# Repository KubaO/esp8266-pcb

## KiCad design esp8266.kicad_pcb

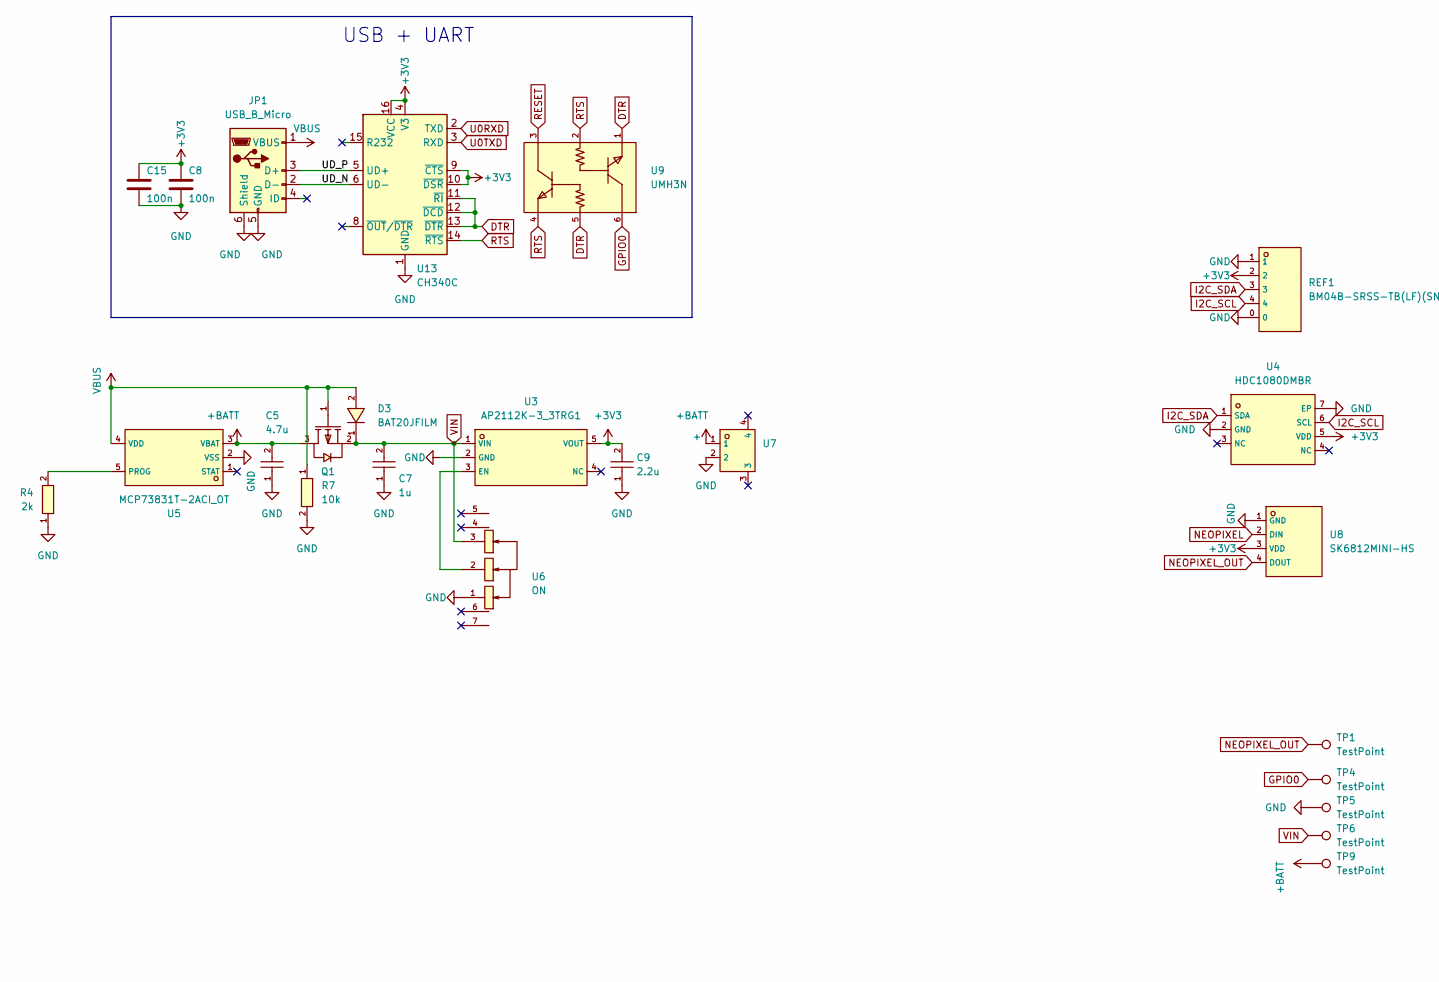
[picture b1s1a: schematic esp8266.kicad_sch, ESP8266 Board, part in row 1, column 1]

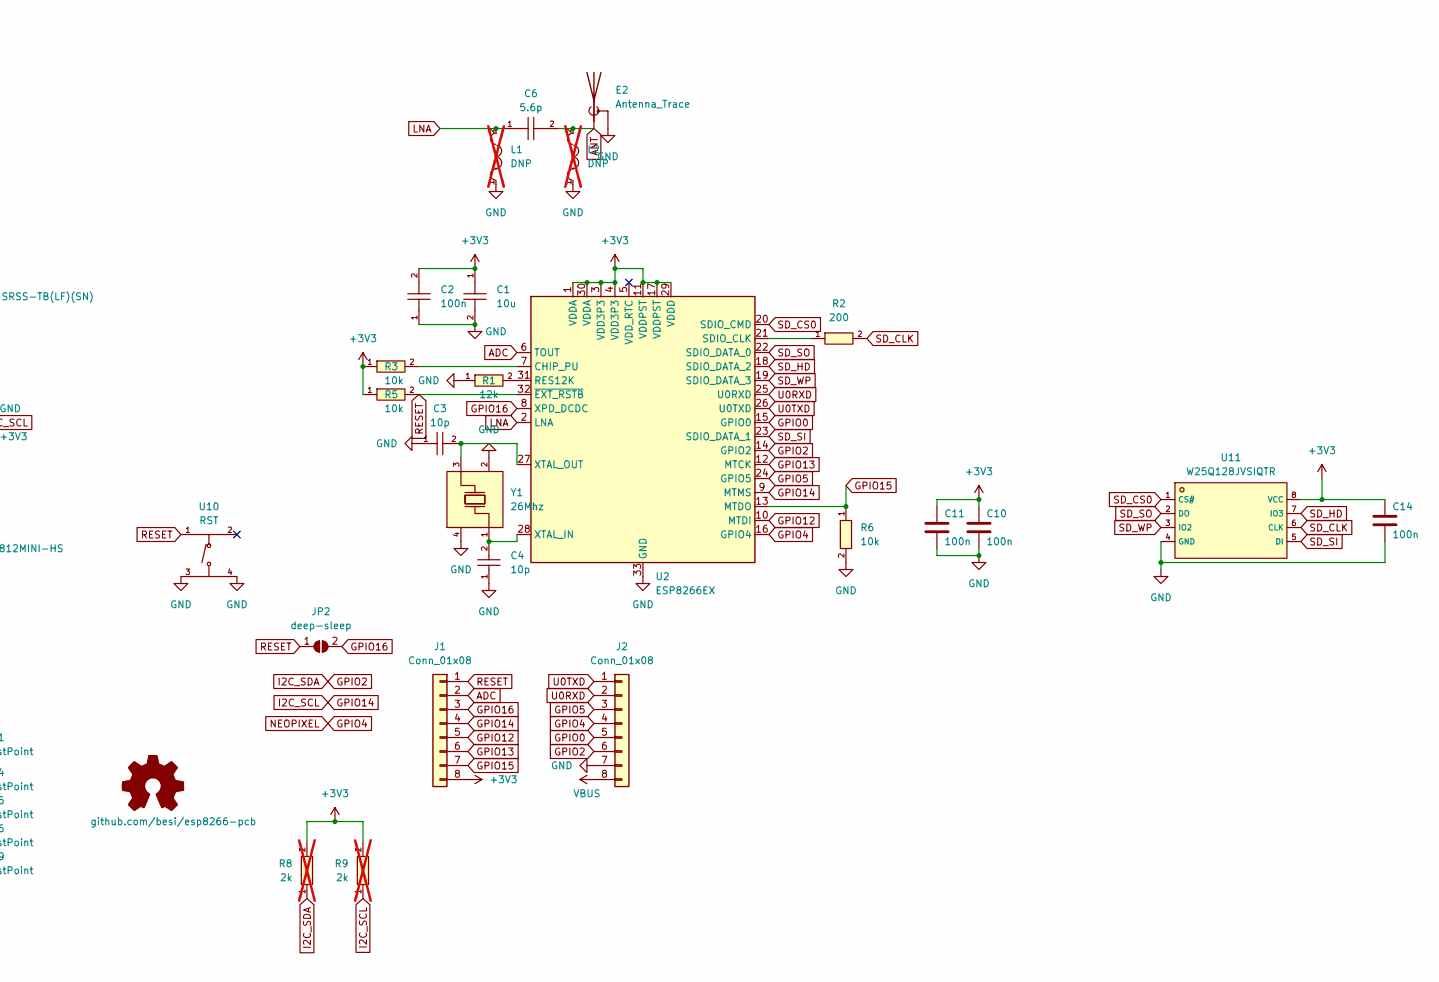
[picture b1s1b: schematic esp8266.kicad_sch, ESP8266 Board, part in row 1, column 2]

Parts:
C1: 10u; C0603; LCSC C19702
C2, C8, C10, C11, C14, C15: 100n; C0603; LCSC C14663
C3, C4: 10p; C0603; LCSC C1634
C5: 4.7u; C0603; LCSC C19666
C6: 5.6p; C0603; LCSC C519111
C7: 1u; C0603; LCSC C15849
C9: 2.2u; C0603; LCSC C23630
D3: BAT20JFILM; SOD-323_L1.8-W1.3-LS2.5-RD; LCSC C155590
E2: Antenna_Trace; Texas_SWRA117D_2.4GHz_Right
J1, J2: Conn_01x08; PinHeader_1x08_P2.54mm_Vertical
JP1: USB_B_Micro; MICRO-USB-SMD_1050171001; LCSC C505111
JP2: deep-sleep; SolderJumper-2_P1.3mm_Open_TrianglePad1.0x1.5mm
L1, L2: DNP; L0603; LCSC C1035; not fitted
OSHW1: github.com/besi/esp8266-pcb; OSHW-Symbol_6.7x6mm_SilkScreen
Q1: AO3401A; SOT-23_L2.9-W1.3-P1.90-LS2.4-BR; LCSC C15127
R1: 12k; R0603; LCSC C22790
R2: 200; R0603; LCSC C8218
R3, R5, R6, R7: 10k; R0603; LCSC C25804
R4: 2k; R0603; LCSC C22975
R8, R9: 2k; R0603; LCSC C22975; not fitted
REF1: BM04B-SRSS-TB(LF)(SN); CONN-SMD_BM04B-SRSS-TB; LCSC C160390
TP1, TP4, TP5, TP6, TP9: TestPoint; TestPoint_Pad_D1.0mm
U2: ESP8266EX; QFN-32_L5.0-W5.0-P0.50-BL-EP3.7
U3: AP2112K-3_3TRG1; SOT-25-5_L2.9-W1.6-P0.95-LS2.8-BL; LCSC C51118
U4: HDC1080DMBR; SENSOR-SMD_HDC1080DMBR; LCSC C82227
U5: MCP73831T-2ACI_OT; SOT-23-5_L3.0-W1.7-P0.95-LS2.8-BL; LCSC C424093
U6: ON; SW-SMD_MK-12C02-G020; LCSC C963206
U7: +; CONN-SMD_P2.00_S2B-PH-SM4-TB-LF-SN; LCSC C295747
U8: SK6812MINI-HS; LED-SMD_4P-L3.5-W3.5-BR_SK6812MINI-HS; LCSC C2922787
U9: UMH3N; SC-70-6_L2.2-W1.3-P0.65-LS2.1-BR; LCSC C62892
U10: RST; SW-SMD_4P-L5.1-W5.1-P3.70-LS6.5-TL-2; LCSC C318884
U11: W25Q128JVSIQTR; SOIC-8_L5.3-W5.3-P1.27-LS8.0-BL; LCSC C97521
U13: CH340C; SOIC-16_3.9x9.9mm_P1.27mm; LCSC C7464026
Y1: 26Mhz; CRYSTAL-SMD_4P-L2.0-W1.6-BL; LCSC C255886

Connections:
+3V3: C1.1, C2.2, C8.2, C9.2, C10.2, C11.2, C14.2, C15.2, J1.8, R3.1, R5.1, R8.2, R9.2, REF1.2, U2.1 (VDDA), U2.3 (VDD3P3), U2.4 (VDD3P3), U2.11 (VDDPST), U2.17 (VDDPST), U2.29 (VDDD), U2.30 (VDDA), U3.5 (VOUT), U4.5 (VDD), U8.3 (VDD), U11.8 (VCC), U13.4 (V3), U13.9 (~CTS), U13.10 (~DSR), U13.16 (VCC)
+BATT: C5.2, Q1.3 (D), TP9.1, U5.3 (VBAT), U7.1
/UD_N: JP1.2 (D-), U13.6 (UD-)
/UD_P: JP1.3 (D+), U13.5 (UD+)
ADC: J1.2, U2.6 (TOUT)
ANT: C6.2, E2.1 (A), L2.2
DTR: U9.1 (E), U9.5 (B), U13.11 (~RI), U13.12 (~DCD), U13.13 (~DTR)
GND: C1.2, C2.1, C3.1, C4.1, C5.1, C7.1, C8.1, C9.1, C10.1, C11.1, C14.1, C15.1, E2.2 (Shield), J2.7, JP1.5 (GND), JP1.6 (Shield), L1.1, L2.1, R1.1, R4.1, R6.2, R7.2, REF1.0, REF1.1, TP5.1, U2.33 (GND), U3.2 (GND), U4.2 (GND), U4.7 (EP), U5.2 (VSS), U6.1, U7.2, U8.1 (GND), U10.3 (C), U10.4 (D), U11.4 (GND), U13.1 (GND), Y1.2 (GND), Y1.4 (GND)
GPIO0: J2.5, TP4.1, U2.15 (GPIO0), U9.6 (C)
GPIO2: J2.6, R8.1, REF1.3, U2.14 (GPIO2), U4.1 (SDA)
GPIO4: J2.4, U2.16 (GPIO4), U8.2 (DIN)
GPIO5: J2.3, U2.24 (GPIO5)
GPIO12: J1.5, U2.10 (MTDI)
GPIO13: J1.6, U2.12 (MTCK)
GPIO14: J1.4, R9.1, REF1.4, U2.9 (MTMS), U4.6 (SCL)
GPIO15: J1.7, R6.1, U2.13 (MTDO)
GPIO16: J1.3, JP2.2 (B), U2.8 (XPD_DCDC)
LNA: C6.1, L1.2, U2.2 (LNA)
NEOPIXEL_OUT: TP1.1, U8.4 (DOUT)
unnamed: R3.2, U2.7 (CHIP_PU)
unnamed: R1.2, U2.31 (RES12K)
unnamed: R2.1, U2.21 (SDIO_CLK)
unnamed: C4.2, U2.28 (XTAL_IN), Y1.1 (OSC1)
unnamed: C3.2, U2.27 (XTAL_OUT), Y1.3 (OSC2)
unnamed: U3.3 (EN), U6.2
unnamed: R4.2, U5.5 (PROG)
RESET: J1.1, JP2.1 (A), R5.2, U2.32 (~EXT_RSTB), U9.3 (C), U10.1 (A)
RTS: U9.2 (B), U9.4 (E), U13.14 (~RTS)
SD_CLK: R2.2, U11.6 (CLK)
SD_CS0: U2.20 (SDIO_CMD), U11.1 (CS#)
SD_HD: U2.18 (SDIO_DATA_2), U11.7 (IO3)
SD_SI: U2.23 (SDIO_DATA_1), U11.5 (DI)
SD_SO: U2.22 (SDIO_DATA_0), U11.2 (DO)
SD_WP: U2.19 (SDIO_DATA_3), U11.3 (IO2)
U0RXD: J2.2, U2.25 (U0RXD), U13.2 (TXD)
U0TXD: J2.1, U2.26 (U0TXD), U13.3 (RXD)
VBUS: D3.2 (A), J2.8, JP1.1 (VBUS), Q1.1 (G), R7.1, U5.4 (VDD)
VIN: C7.2, D3.1 (K), Q1.2 (S), TP6.1, U3.1 (VIN), U6.3

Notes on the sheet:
USB + UART

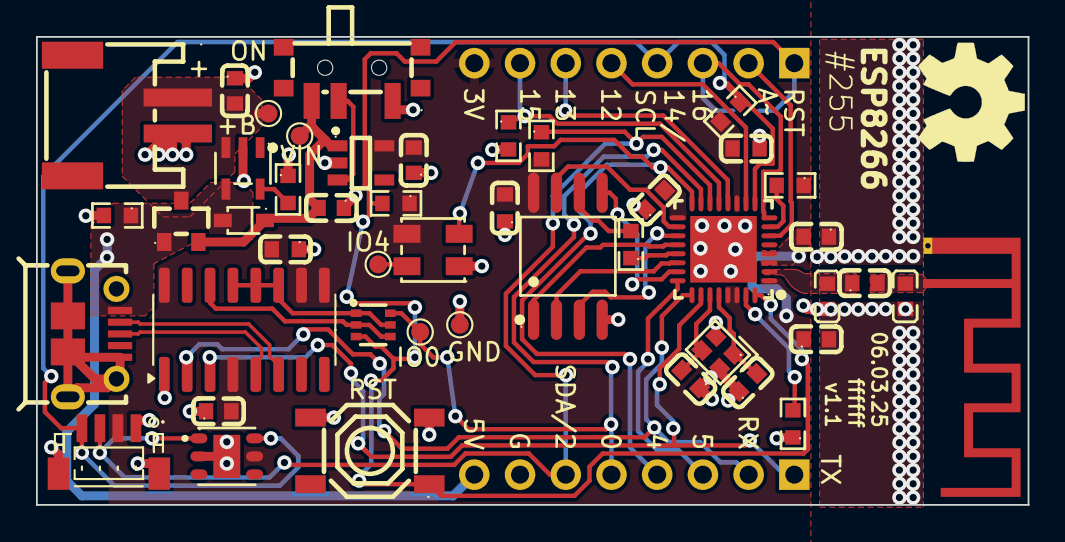
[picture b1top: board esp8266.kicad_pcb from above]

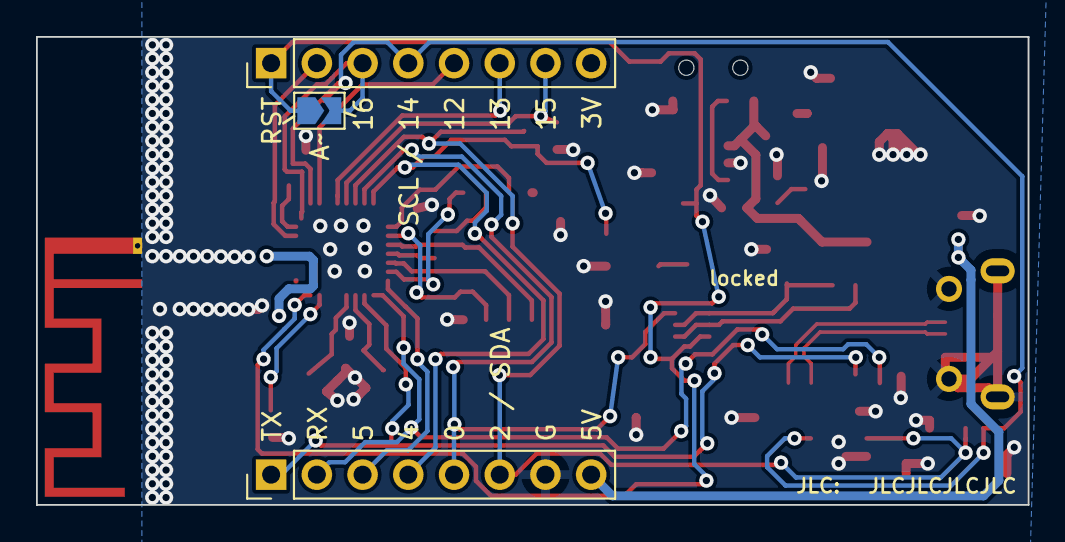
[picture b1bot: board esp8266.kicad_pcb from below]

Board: 2 copper layers, 55.1 x 26.0 mm, 50 parts (3 on the bottom side), 38 nets.

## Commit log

2025-03-06 Fix 3D model positioning and paths.
2025-03-06 Rework layout to retain power and ground plane continuity.
    Add one more decoupling capacitor to CH340.
    The ground plane now has islands of shorter traces. The 3.3V plane has been carefully adjusted to provide reasonable impedances to all loads.
